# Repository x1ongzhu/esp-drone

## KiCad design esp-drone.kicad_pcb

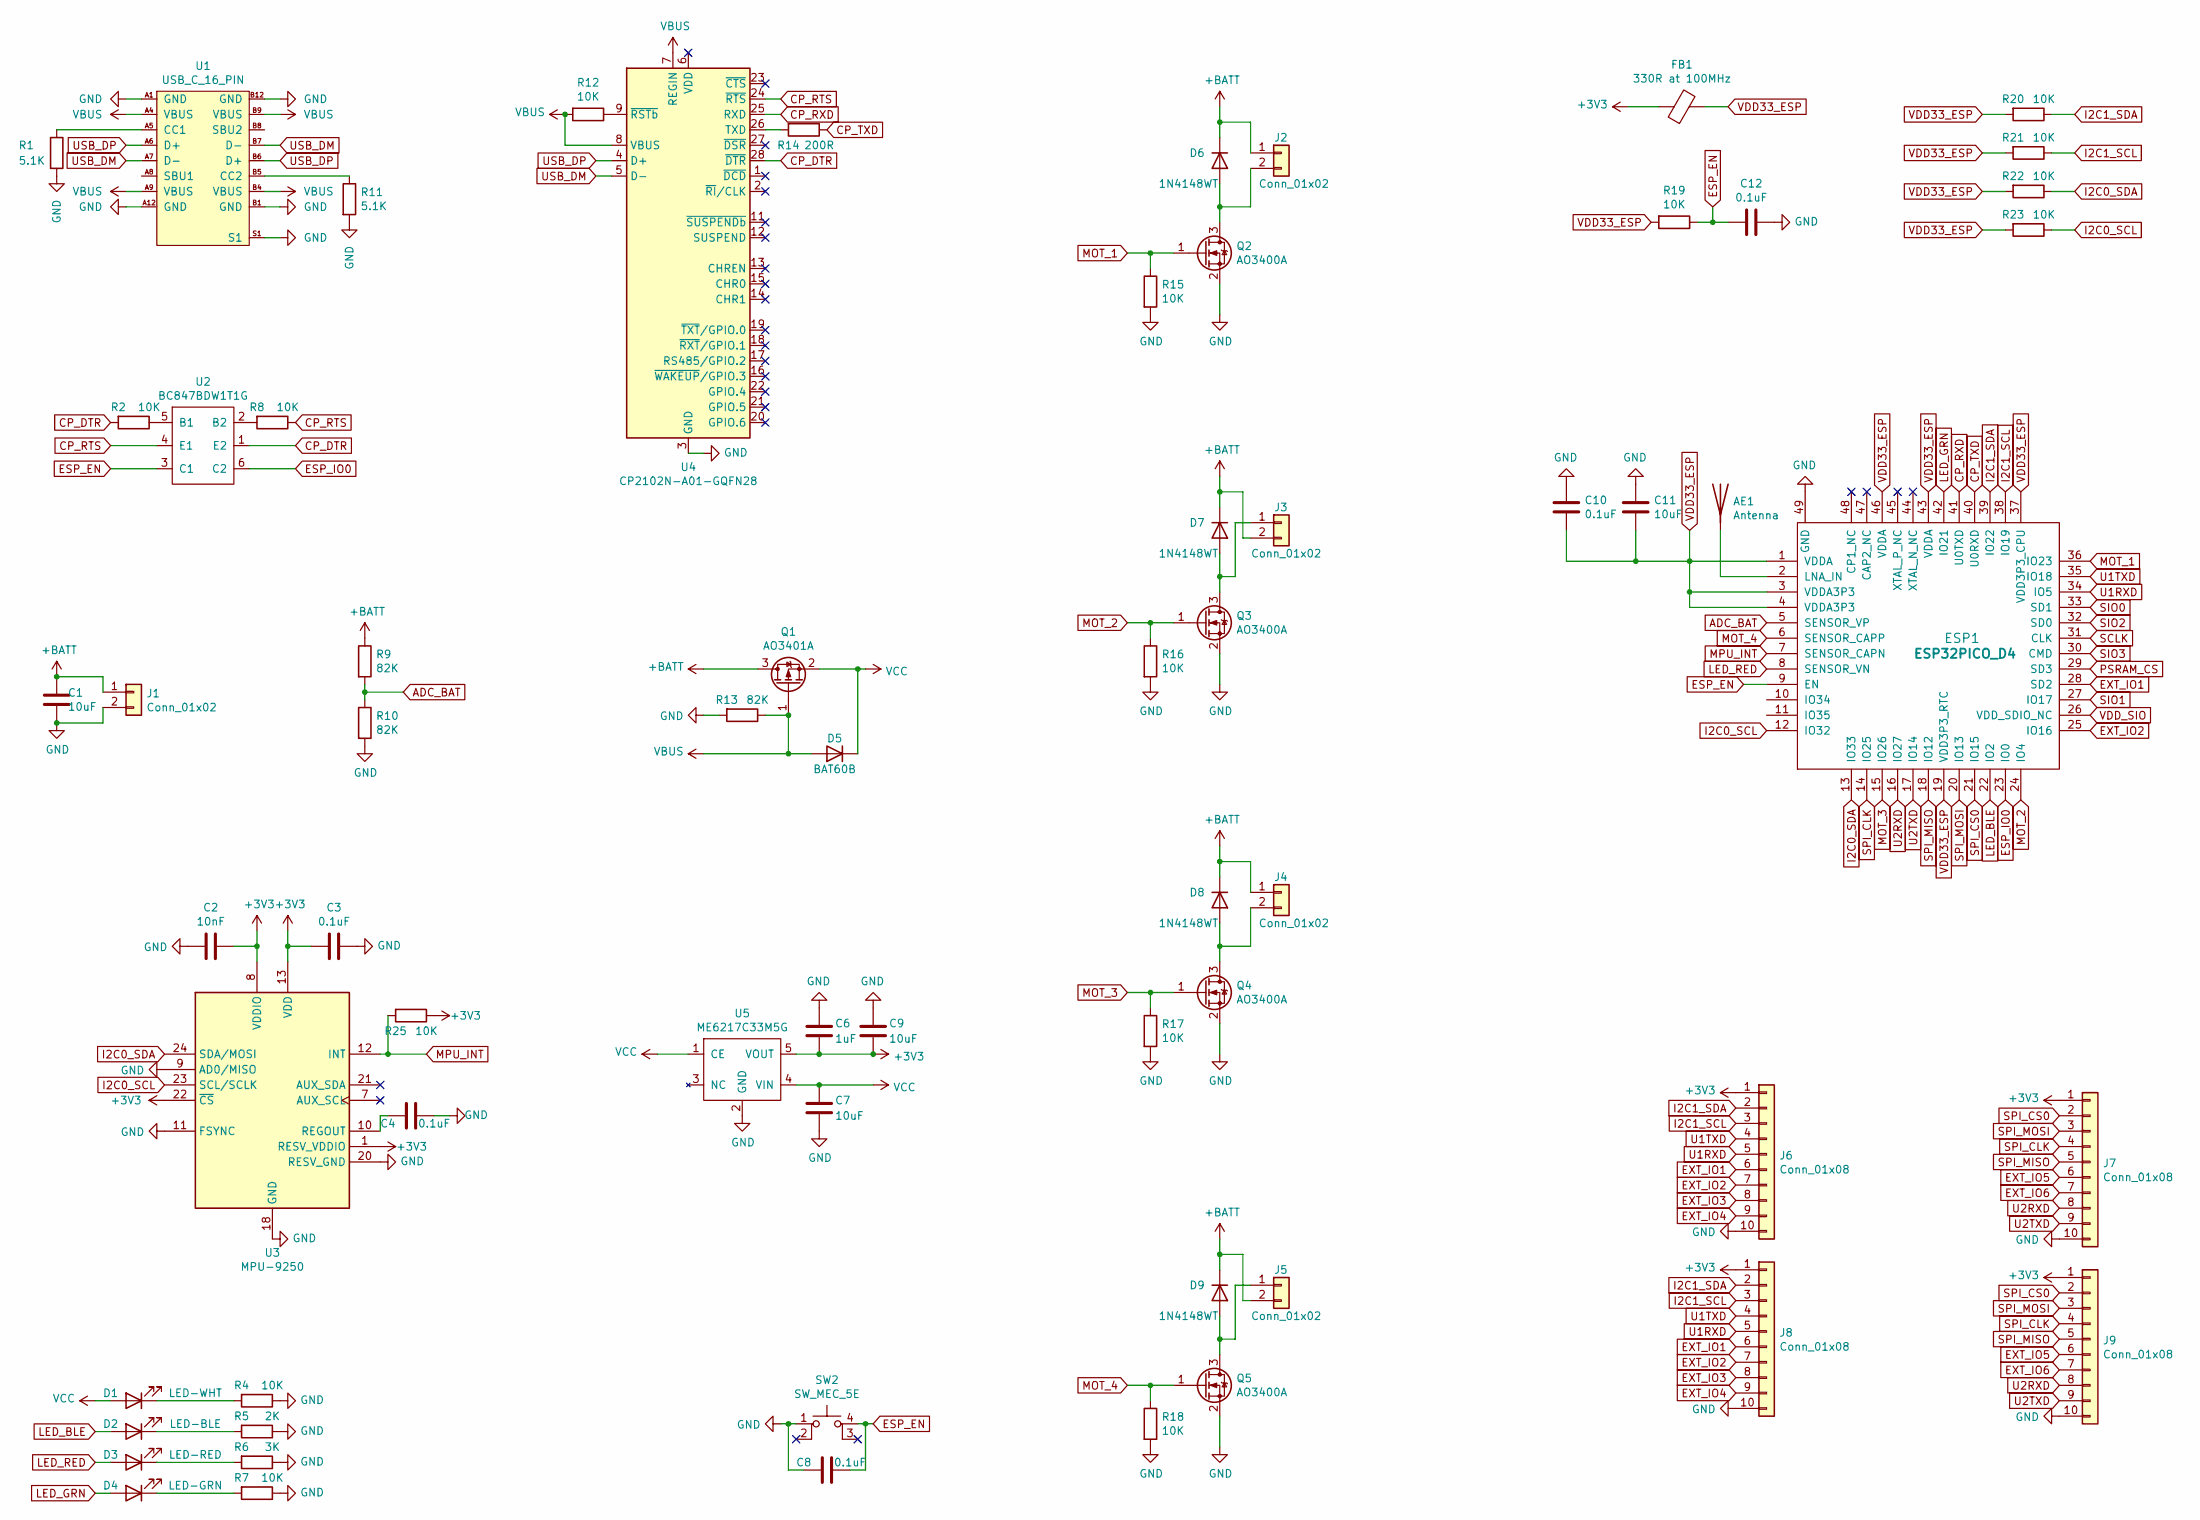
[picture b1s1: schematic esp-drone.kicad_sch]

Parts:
AE1: Antenna; CA-C03
C1: 10uF; R_0402_1005Metric
C2: 10nF; C_0402_1005Metric
C3, C4, C8, C10, C12: 0.1uF; C_0402_1005Metric
C6: 1uF; C_0402_1005Metric
C7, C9, C11: 10uF; C_0402_1005Metric
D1: LED-WHT; LED_0402_1005Metric
D2: LED-BLE; LED_0402_1005Metric
D3: LED-RED; LED_0402_1005Metric
D4: LED-GRN; LED_0402_1005Metric
D5: BAT60B; D_SOD-323
D6, D7, D8, D9: 1N4148WT; D_SOD-523
ESP1: ESP32PICO_D4; ESP32_PICO_D4
FB1: 330R at 100MHz; R_0402_1005Metric
J1: Conn_01x02; JST_PH_S2B-PH-K_1x02_P2.00mm_Horizontal
J2, J3, J4, J5: Conn_01x02; MX1.25_2P
J6, J7: Conn_01x08; PinHeader_1x10_P2.00mm_Vertical_SMD_Pin1Right
J8, J9: Conn_01x08; 1x10_P2.0
Q1: AO3401A; SOT-23
Q2, Q3, Q4, Q5: AO3400A; SOT-23
R1, R11: 5.1K; R_0402_1005Metric
R2, R4, R7, R8, R12, R15, R16, R17, R18, R19, R20, R21, R22, R23, R25: 10K; R_0402_1005Metric
R5: 2K; R_0402_1005Metric
R6: 3K; R_0402_1005Metric
R9, R10, R13: 82K; R_0402_1005Metric
R14: 200R; R_0402_1005Metric
SW2: SW_MEC_5E; SKSC_NO_HOLE
U1: USB_C_16_PIN; USB_C_Receptacle_HRO_TYPE-C-31-M-12
U2: BC847BDW1T1G; SOT-563
U3: MPU-9250; InvenSense_QFN-24_3x3mm_P0.4mm
U4: CP2102N-A01-GQFN28; QFN-28-1EP_5x5mm_P0.5mm_EP3.35x3.35mm
U5: ME6217C33M5G; SOT-23-5

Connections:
+3V3: C2.2, C3.1, C6.2, C9.2, FB1.1, J6.1, J7.1, J8.1, J9.1, R25.1, U3.1 (RESV_VDDIO), U3.8 (VDDIO), U3.13 (VDD), U3.22 (~CS), U5.5 (VOUT)
+BATT: C1.1, D6.1 (K), D7.1 (K), D8.1 (K), D9.1 (K), J1.1, J2.1, J3.2, J4.1, J5.2, Q1.3 (D), R9.1
ADC_BAT: ESP1.5 (SENSOR_VP), R9.2, R10.1
CP_DTR: R2.2, U2.1 (E2), U4.28 (~DTR)
CP_RTS: R8.1, U2.4 (E1), U4.24 (~RTS)
CP_RXD: ESP1.41 (U0TXD), U4.25 (RXD)
CP_TXD: ESP1.40 (U0RXD), R14.1
ESP_EN: C8.1, C12.2, ESP1.9 (EN), R19.1, SW2.4 (A), U2.3 (C1)
ESP_IO0: ESP1.23 (IO0), U2.6 (C2)
EXT_IO1: ESP1.28 (SD2), J6.6, J8.6
EXT_IO2: ESP1.25 (IO16), J6.7, J8.7
EXT_IO3: J6.8, J8.8
EXT_IO4: J6.9, J8.9
EXT_IO5: J7.6, J9.6
EXT_IO6: J7.7, J9.7
GND: C1.2, C2.1, C3.2, C4.1, C6.1, C7.2, C8.2, C9.1, C10.1, C11.1, C12.1, ESP1.49 (GND), J1.2, J6.10, J7.10, J8.10, J9.10, Q2.2 (S), Q3.2 (S), Q4.2 (S), Q5.2 (S), R1.2, R4.1, R5.1, R6.1, R7.1, R10.2, R11.2, R13.2, R15.2, R16.2, R17.2, R18.2, SW2.1, U1.A1 (GND), U1.A12 (GND), U1.B1 (GND), U1.B12 (GND), U1.S1, U3.9 (AD0/MISO), U3.11 (FSYNC), U3.18 (GND), U3.20 (RESV_GND), U4.3 (GND), U4.29 (GND), U5.2 (GND)
I2C0_SCL: ESP1.12 (IO32), R23.1, U3.23 (SCL/SCLK)
I2C0_SDA: ESP1.13 (IO33), R22.1, U3.24 (SDA/MOSI)
I2C1_SCL: ESP1.38 (IO19), J6.3, J8.3, R21.1
I2C1_SDA: ESP1.39 (IO22), J6.2, J8.2, R20.1
LED_BLE: D2.2 (A), ESP1.22 (IO2)
LED_GRN: D4.2 (A), ESP1.42 (IO21)
LED_RED: D3.2 (A), ESP1.8 (SENSOR_VN)
MOT_1: ESP1.36 (IO23), Q2.1 (G), R15.1
MOT_2: ESP1.24 (IO4), Q3.1 (G), R16.1
MOT_3: ESP1.15 (IO26), Q4.1 (G), R17.1
MOT_4: ESP1.6 (SENSOR_CAPP), Q5.1 (G), R18.1
MPU_INT: ESP1.7 (SENSOR_CAPN), R25.2, U3.12 (INT)
unnamed: AE1.1 (A), ESP1.2 (LNA_IN)
unnamed: C4.2, U3.10 (REGOUT)
unnamed: D1.1 (K), R4.2
unnamed: D2.1 (K), R5.2
unnamed: D3.1 (K), R6.2
unnamed: D4.1 (K), R7.2
unnamed: D6.2 (A), J2.2, Q2.3 (D)
unnamed: D7.2 (A), J3.1, Q3.3 (D)
unnamed: D8.2 (A), J4.2, Q4.3 (D)
unnamed: D9.2 (A), J5.1, Q5.3 (D)
unnamed: R1.1, U1.A5 (CC1)
unnamed: R2.1, U2.5 (B1)
unnamed: R8.2, U2.2 (B2)
unnamed: R11.1, U1.B5 (CC2)
unnamed: R12.1, U4.9 (~RSTb)
unnamed: R14.2, U4.26 (TXD)
PSRAM_CS: ESP1.29 (SD3)
SCLK: ESP1.31 (CLK)
SIO0: ESP1.33 (SD1)
SIO1: ESP1.27 (IO17)
SIO2: ESP1.32 (SD0)
SIO3: ESP1.30 (CMD)
SPI_CLK: ESP1.14 (IO25), J7.4, J9.4
SPI_CS0: ESP1.21 (IO15), J7.2, J9.2
SPI_MISO: ESP1.18 (IO12), J7.5, J9.5
SPI_MOSI: ESP1.20 (IO13), J7.3, J9.3
U1RXD: ESP1.34 (IO5), J6.5, J8.5
U1TXD: ESP1.35 (IO18), J6.4, J8.4
U2RXD: ESP1.16 (IO27), J7.8, J9.8
U2TXD: ESP1.17 (IO14), J7.9, J9.9
USB_DM: U1.A7 (D-), U1.B7 (D-), U4.5 (D-)
USB_DP: U1.A6 (D+), U1.B6 (D+), U4.4 (D+)
VBUS: D5.2 (A), Q1.1 (G), R12.2, R13.1, U1.A4 (VBUS), U1.A9 (VBUS), U1.B4 (VBUS), U1.B9 (VBUS), U4.7 (REGIN), U4.8 (VBUS)
VCC: C7.1, D1.2 (A), D5.1 (K), Q1.2 (S), U5.1 (CE), U5.4 (VIN)
VDD33_ESP: C10.2, C11.2, ESP1.1 (VDDA), ESP1.3 (VDDA3P3), ESP1.4 (VDDA3P3), ESP1.19 (VDD3P3_RTC), ESP1.37 (VDD3P3_CPU), ESP1.43 (VDDA), ESP1.46 (VDDA), FB1.2, R19.2, R20.2, R21.2, R22.2, R23.2
VDD_SIO: ESP1.26 (VDD_SDIO_NC)

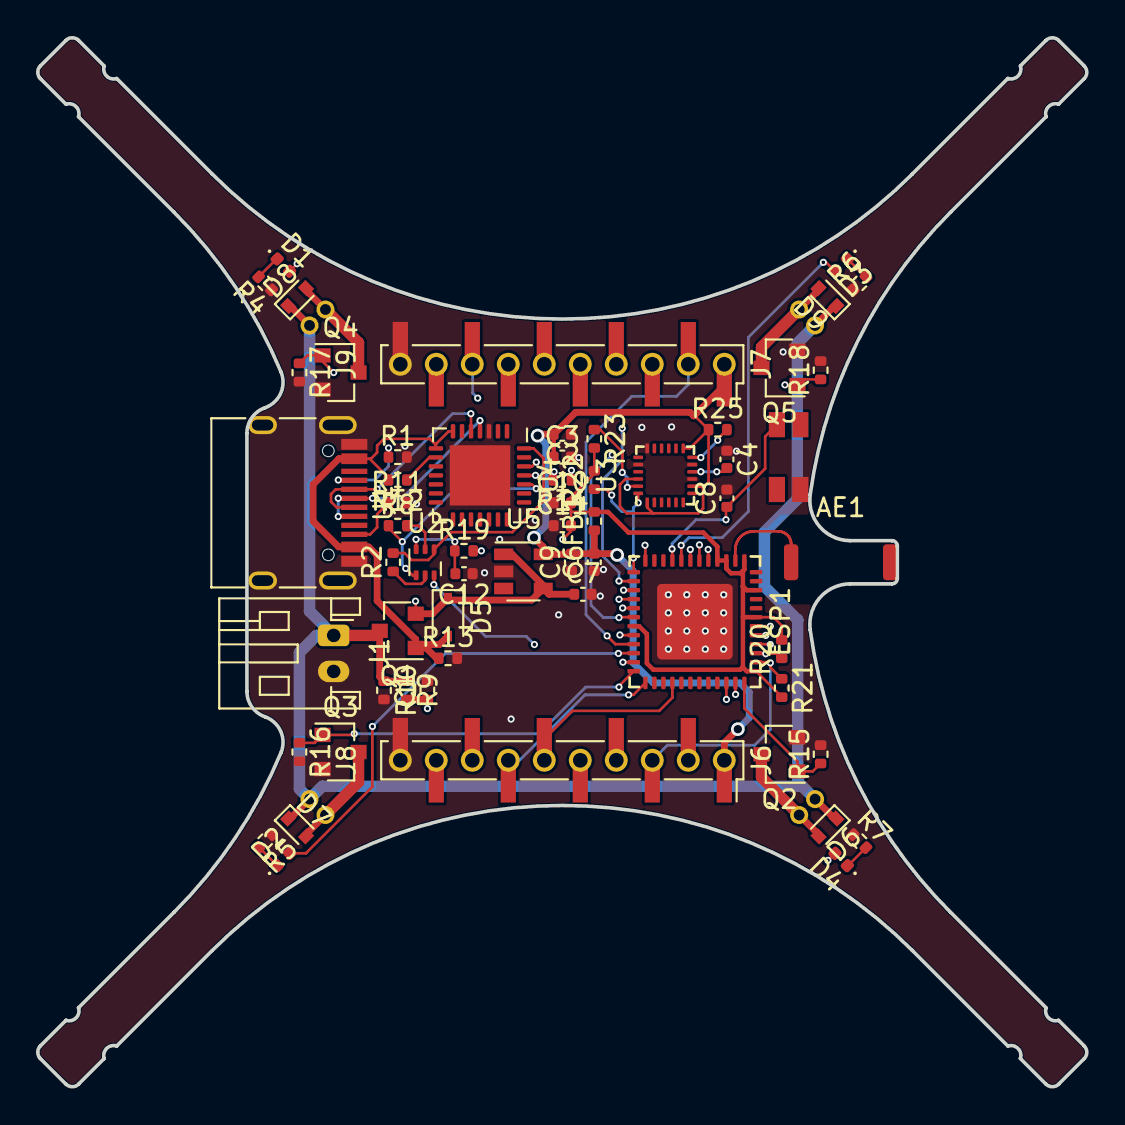
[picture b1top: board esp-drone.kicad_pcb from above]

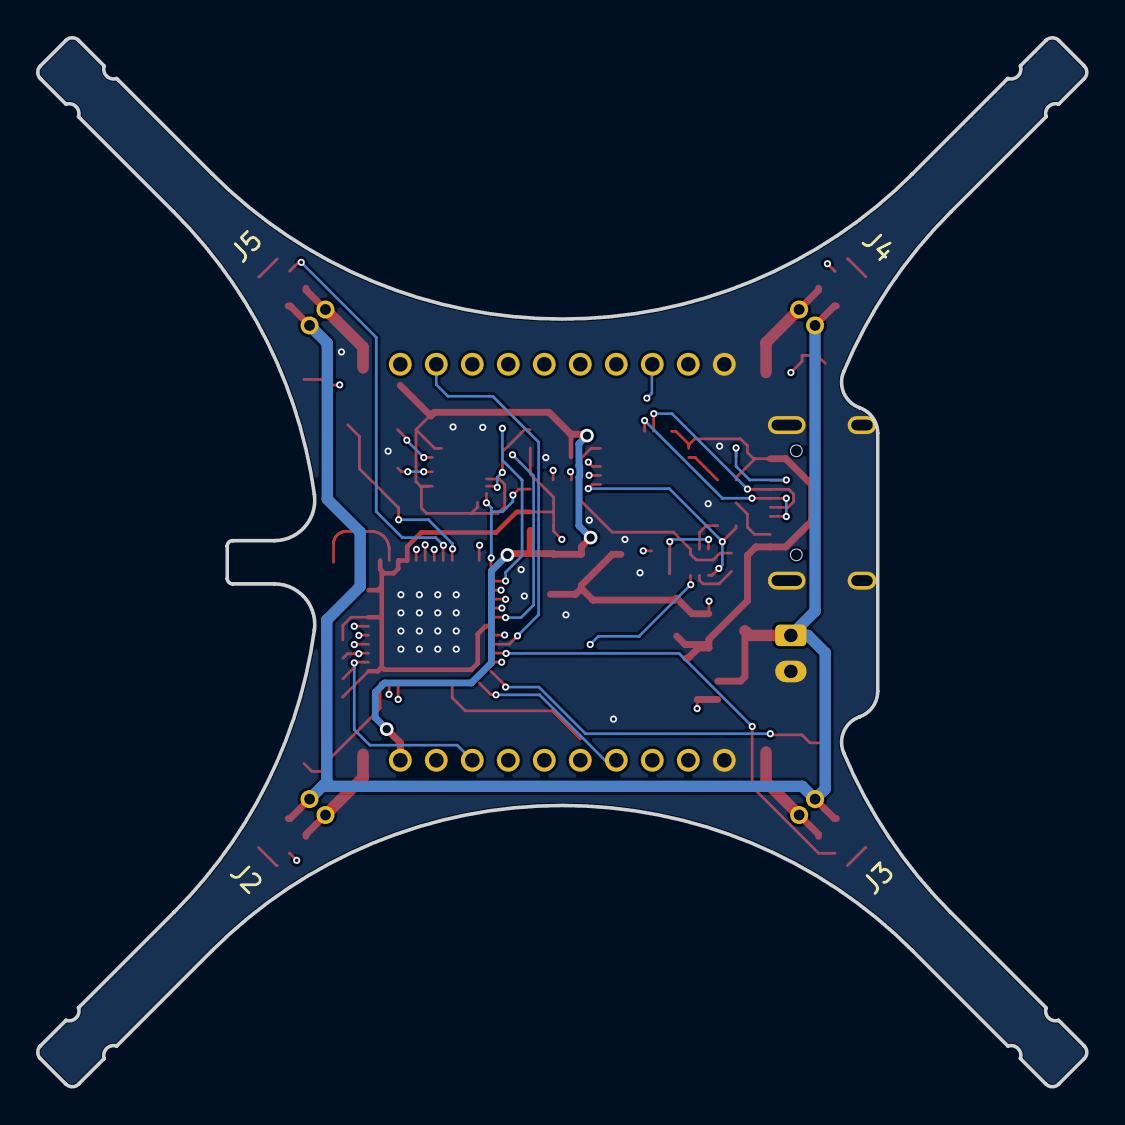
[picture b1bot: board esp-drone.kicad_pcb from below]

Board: 4 copper layers, 58.3 x 58.3 mm, 66 parts (4 on the bottom side), 57 nets.

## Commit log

2021-10-17 sch finish
